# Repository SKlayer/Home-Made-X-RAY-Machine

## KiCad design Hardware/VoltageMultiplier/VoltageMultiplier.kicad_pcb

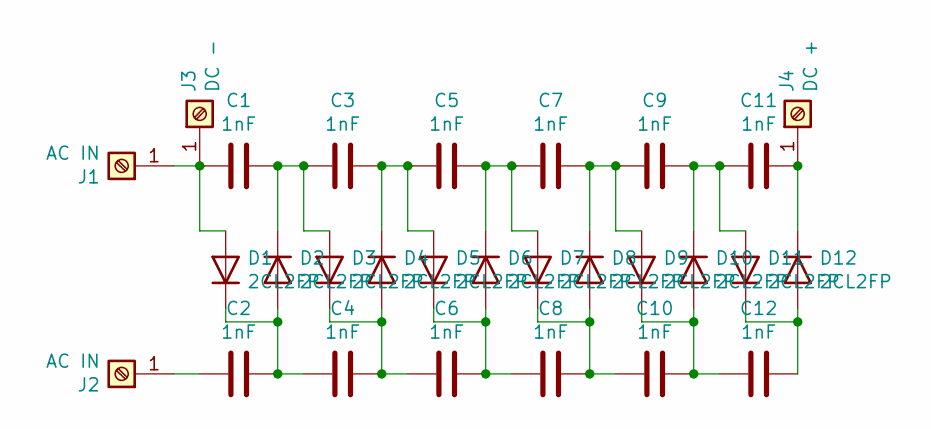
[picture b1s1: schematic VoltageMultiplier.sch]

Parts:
C1, C2, C3, C4, C5, C6, C7, C8, C9, C10, C11, C12: 1nF; C_Rect_L16.5mm_W13.9mm_P15.00mm_MKT
D1, D2, D3, D4, D5, D6, D7, D8, D9, D10, D11, D12: 2CL2FP; D_P600_R-6_P20.00mm_Horizontal
J1, J2: AC IN; SolderWire-2.5sqmm_1x01_D2.4mm_OD3.6mm
J3: DC -; SolderWire-2.5sqmm_1x01_D2.4mm_OD3.6mm
J4: DC +; SolderWire-2.5sqmm_1x01_D2.4mm_OD3.6mm

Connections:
unnamed: C1.1, D1.2 (A), J1.1, J3.1
unnamed: C1.2, C3.1, D2.1 (K), D3.2 (A)
unnamed: C2.1, J2.1
unnamed: C2.2, C4.1, D1.1 (K), D2.2 (A)
unnamed: C3.2, C5.1, D4.1 (K), D5.2 (A)
unnamed: C4.2, C6.1, D3.1 (K), D4.2 (A)
unnamed: C5.2, C7.1, D6.1 (K), D7.2 (A)
unnamed: C6.2, C8.1, D5.1 (K), D6.2 (A)
unnamed: C7.2, C9.1, D8.1 (K), D9.2 (A)
unnamed: C8.2, C10.1, D7.1 (K), D8.2 (A)
unnamed: C10.2, C12.1, D9.1 (K), D10.2 (A)
unnamed: C9.2, C11.1, D10.1 (K), D11.2 (A)
unnamed: C11.2, D12.1 (K), J4.1
unnamed: C12.2, D11.1 (K), D12.2 (A)

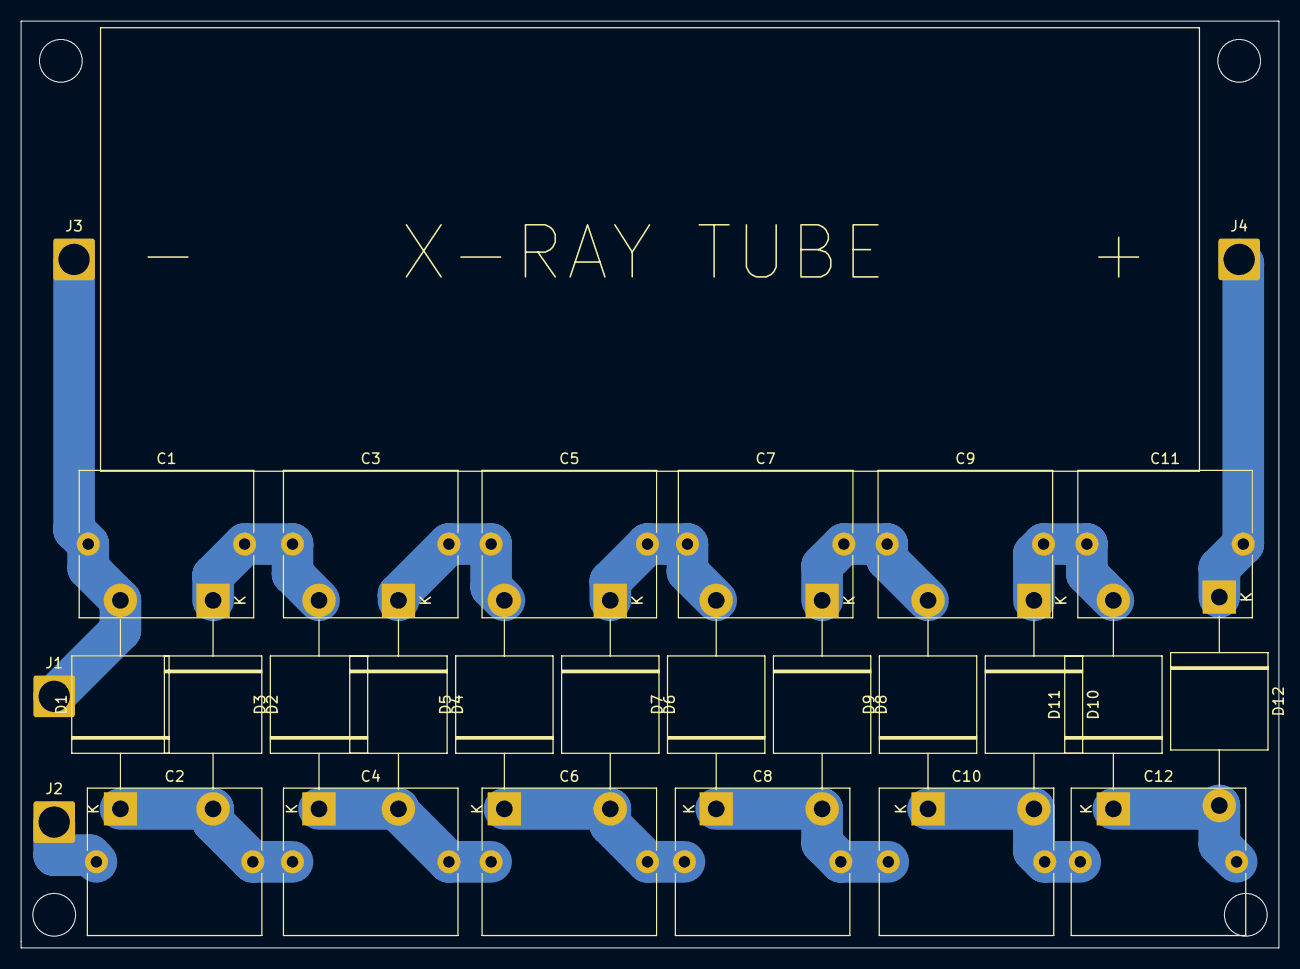
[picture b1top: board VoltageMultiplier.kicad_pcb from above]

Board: 2 copper layers, 120.7 x 88.9 mm, 28 parts (0 on the bottom side), 14 nets.

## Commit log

2021-01-24 2nd commit
2021-01-24 Arduino librarys commit
